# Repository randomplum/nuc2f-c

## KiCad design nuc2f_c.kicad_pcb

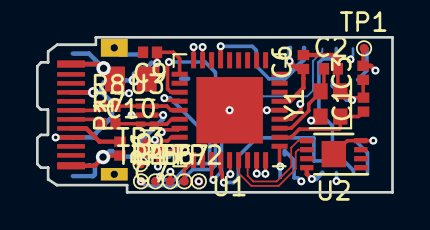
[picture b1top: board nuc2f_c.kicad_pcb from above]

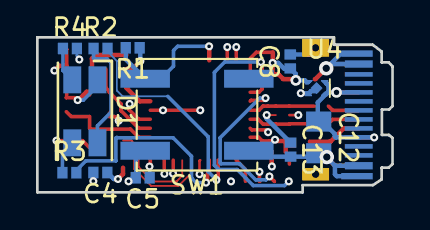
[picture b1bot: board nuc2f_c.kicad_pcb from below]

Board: 4 copper layers, 19.7 x 8.6 mm, 34 parts (12 on the bottom side), 25 nets.

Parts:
C1, C2: 27p; C_0402_1005Metric
C3, C4, C5, C6, C7, C8, C9, C13: 100n; C_0402_1005Metric
C10, C12: 2u2; C_0805_2012Metric
D1: LED_ARGB; LED_RGB_1210
P1: USB_C_Plug; USB_C_Plug_JAE_DX07P024AJ1
R1: 10k; R_0402_1005Metric
R2, R3, R4: 1k; R_0402_1005Metric
R6: 5k1; R_0402_1005Metric
R7, R8: 22R; R_0402_1005Metric
SW1: SW_Push; SW_SPST_EVQP0
TP1: RST; TestPoint_Pad_D0.5mm
TP2: 3.3V; TestPoint_Pad_D0.5mm
TP3: GND; TestPoint_Pad_D0.5mm
TP4: TX; TestPoint_Pad_D0.5mm
TP5: RX; TestPoint_Pad_D0.5mm
TP6: SWDIO; TestPoint_Pad_D0.5mm
TP7: SWCLK; TestPoint_Pad_D0.5mm
U1: STM32F103TBUx; QFN-36-1EP_6x6mm_P0.5mm_EP3.7x3.7mm
U2: ATECC508A; DFN-8-1EP_3x2mm_P0.5mm_EP1.36x1.46mm
U3: USBULC6-2M6; Fairchild_MicroPak-6_1.0x1.45mm_P0.5mm
U4: NCP114; UDFN-4_1x1mm_P0.65mm
Y1: 8MHz; Crystal_SMD_2016-4Pin_2.0x1.6mm

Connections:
+3V3: C4.1, C5.1, C6.1, C7.1, C8.1, C9.1, C10.1, R1.1, TP2.1, U1.1, U1.6, U1.19, U1.27, U2.8, U4.1
+5V: C12.1, P1.A4, P1.A9, P1.B4, P1.B9, U4.3, U4.4
/D+: R7.2, U1.24, U3.3, U3.4
/D-: R8.2, U1.23, U3.1, U3.6
/I2C_SCL: U1.33, U2.6
/I2C_SDA: U1.34, U2.5
GND: C1.2, C2.2, C3.1, C4.2, C5.2, C6.2, C7.2, C8.2, C9.2, C10.2, C12.2, C13.2, D1.1, P1.A1, P1.A12, P1.B1, P1.B12, P1.S1, R6.2, SW1.1, TP3.1, U1.5, U1.17, U1.18, U1.26, U1.35, U1.36, U1.37, U2.4, U2.9, U3.2, U4.2, U4.5, Y1.2, Y1.4
unnamed: C1.1, U1.2, Y1.1
unnamed: C2.1, U1.3, Y1.3
unnamed: C3.2, TP1.1, U1.4
unnamed: C13.1, U3.5
unnamed: D1.2, R4.1
unnamed: D1.3, R3.1
unnamed: D1.4, R2.1
unnamed: P1.A5, R6.1
unnamed: P1.A6, R7.1
unnamed: P1.A7, R8.1
unnamed: R1.2, SW1.2, U1.15
unnamed: R2.2, U1.30
unnamed: R3.2, U1.31
unnamed: R4.2, U1.32
unnamed: TP4.1, U1.21
unnamed: TP5.1, U1.22
unnamed: TP6.1, U1.25
unnamed: TP7.1, U1.28

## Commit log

2018-04-23 NUC2F-C component identification
    Include all components to be used in the design.
    (passives not included)
2018-04-23 NUC2F-C complete schematics v1
2018-04-24 NUK2F-C assign footprints
2018-04-24 NUK2F-C schematics v2
    Remove power led and few capacitors.
2018-04-24 NUC2F-C PCB design v1
2019-11-26 NUC2F-C fix PCB outline
2019-11-26 NUC2F-C fix plane fill
2019-11-26 NUC2F-C v2
    -fix rgb led common voltage
    -missing gnd connection on C9
    -usb D+ pull-up resistor
